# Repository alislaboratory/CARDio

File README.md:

# CARDio: a heart-rate monitor business card

**CARDio** is a PCB business card with a built-in heart-rate monitor. Put your thumb on the sensor and a nervous system drawn in silkscreen lights up in time with your heartbeat, coloured by your heart rate. Lift your thumb and it counts your BPM out on the LEDs.

- **ESP32-C3** (RISC-V, Wi-Fi + BLE) with native USB: one USB-C cable powers and programs it.
- **MAX30102** optical pulse sensor under the "Place Thumb" pad.
- **13 addressable RGB LEDs**: 11 along the brain, spinal cord and nerve roots, and 2 on the back as bullet points for the name and URL.
- Credit-card sized, 4-layer, black and white. Designed in EasyEDA, now also a **KiCad 10** project.

## Using it

1. **Plug it in** with a USB-C cable (any phone charger or computer). A spark climbs the spinal cord, the brain lights up, and the card gives its first heartbeat.
2. **Idle:** the tree glows softly like starlight.
3. **Rest your thumb** lightly on the "Place Thumb" pad and keep still. A violet scan sweeps upward while it finds your pulse. After 5 to 10 seconds, each real heartbeat sends a wave up the tree. The colour tells you the rate:
   - **Blue:** under 60
   - **Teal/green:** resting
   - **Amber:** around 100
   - **Red:** 130+
4. **Lift your thumb** to see your number, counted out from the bottom up one digit at a time. For 72 bpm, 7 lights come on, then a pause, then 2 white lights. A zero shows as one soft flash of the whole tree.

If it doesn't find your pulse, press more lightly and hold still. Warm hands work better than cold ones.

## Repository layout

| | |
| --- | --- |
| [`firmware/`](firmware/) | The firmware (PlatformIO, Arduino on ESP32-C3): heart-rate detection, LED animations, and the boot-pin workaround. [Details →](firmware/README.md) |
| [`hardware/`](hardware/) | KiCad project, original EasyEDA sources, Gerbers/BOM/CPL for ordering, pin map, LED map and errata. [Details →](hardware/README.md) |
| [`docs/images/`](docs/images/) | Photos and renders |
| [`legacy/`](legacy/) | Early Arduino sketches from bring-up, kept for reference |

## Flashing the firmware

Install [PlatformIO](https://platformio.org/) (the VS Code extension or the CLI), plug the card in, then:

```bash
cd firmware
pio run -t upload
```

That's it: no buttons, no adapters. The ESP32-C3 programs over its own USB port. `pio device monitor` opens a serial console. Type `help` for commands, such as `status`, a live `plot` of the sensor signal, or `demo 72` to show off the LEDs without a thumb.

## Why?

I had tinkered with the idea of PCB business cards in the past. My first iteration was essentially just a blank PCB with a silkscreen. It did have circuitry for an ATtiny85 and some NeoPixels, though I never got it to work properly. I liked the idea of handing a business card to somebody that wouldn't be thrown away: one that would actually have a use, like an NFC tag, flashing lights, or an ECG. Perhaps this was a little overkill, but I wanted something to hand to medical professionals or surgeons at conferences that would leave a memorable impression. It also demonstrates my interest in combining medicine and technology, in this case embedded electronics.

## How it works

This was my first PCB that actually does something, so it's not very complicated. USB-C powers the board through two LDOs: one for 3.3 V (the ESP32-C3 and the LEDs) and one for 1.8 V (the MAX30102 sensor). Most of the passive components are the boilerplate to get the microcontroller running. The MAX30102 talks to the ESP32-C3 over I²C, and the RGB LEDs share a single data wire, daisy-chained together. The ESP32-C3 has a built-in USB programmer, so it doesn't need any extra circuitry for that.

The firmware shines infrared light into your thumb and watches how much comes back. Each heartbeat pushes a little more blood into the thumb, which absorbs a little more light, so the signal dips once per beat. It filters that signal, picks out each beat, rejects anything that doesn't fit a steady rhythm, and only shows a heart rate once it has five consistent beats in a row. The [firmware README](firmware/README.md#how-the-heart-rate-is-measured) has the details.

### The one thing that went wrong

Everything worked on the first batch, except for one mistake: the sensor's I²C lines are wired to the ESP32-C3's **boot-mode strapping pins** (GPIO8/9). If the chip resets in the middle of talking to the sensor, it can boot into its bootloader instead of the program, and the card looks dead until you unplug it. The current firmware works around this completely, and the [hardware notes](hardware/README.md#errata-and-ideas-for-rev-31) list it with the other fixes for the next revision.

### Why "Rev 3.0"?

My previous designs were:

- **Rev 1.0:** a simple blank board with a layout for an ATtiny to control LEDs (non-functional)
- **Rev 2.0:** a PCB business card that runs Linux using Onion Omega2 SBCs (not completed)
- **Rev 3.0 (this one):** a PCB business card that measures your heart rate (complete)

## Ideas for Rev 3.1

- Battery (coin cell) and maybe charging
- A small 0.91" OLED for the ECG trace and numbers
- More sensors
- The hardware fixes in the [errata](hardware/README.md#errata-and-ideas-for-rev-31): I²C off the strap pins, a ground plane, and an EN reset capacitor

## License

[MIT](LICENSE), covering the firmware, tools and hardware design files. Build your own, remix it, put your own name on the back.

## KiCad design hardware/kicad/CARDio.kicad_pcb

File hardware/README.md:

# CARDio hardware (Rev 3.0)

A credit-card-sized PCB: an ESP32-C3 reads a MAX30102 pulse sensor under your thumb and drives 13 RGB LEDs, 11 of them laid out along a brain, spinal cord and nerve roots drawn in silkscreen. Power and programming are both over USB-C.

| | |
| --- | --- |
| Size | 85.85 × 54.23 mm (credit card), 1.6 mm, 4 copper layers |
| Finish | Black solder mask, white silkscreen, HASL |
| MCU | ESP32-C3FH4: RISC-V, Wi-Fi + BLE, 4 MB embedded flash, 40 MHz crystal |
| Sensor | MAX30102 pulse oximetry / heart-rate sensor (I²C) |
| LEDs | 13 × WS2812B-2020 addressable RGB (11 front, 2 back) + green power LED |
| USB | USB-C, power + the C3's native USB-Serial/JTAG (no USB-UART chip), USBLC6-2SC6 ESD protection |
| Power | 5 V USB → AMS1117-3.3 (MCU, LEDs, sensor LEDs) and AMS1117-1.8 (sensor core) |
| Antenna | On-board inverted-F PCB antenna (ANT1) |

## Files

| Folder | What's in it |
| --- | --- |
| [`kicad/`](kicad/) | **The KiCad 10 project**: schematic, PCB, design rules, and project-local symbol and footprint libraries (`CARDio.kicad_sym`, `CARDio.pretty`), so it opens anywhere without extra libraries. Start here to modify the board. |
| [`CARDio_schematic.pdf`](CARDio_schematic.pdf) | The schematic as a PDF |
| [`fabrication/`](fabrication/) | What the cards were made from: Gerbers + drill (`CARDio_Rev3.0_gerbers.zip`), BOM and pick-and-place (CPL) for JLCPCB assembly. |
| [`easyeda/`](easyeda/) | The original EasyEDA Standard sources the board was designed in (open them via *File → Open → EasyEDA…* in EasyEDA). |
| [`tools/`](tools/) | The scripts used to convert the design to KiCad and to verify the conversion. |

## Block diagram

```mermaid
flowchart LR
    USB["USB-C<br/>(5 V, D+/D−)"] --> ESD["USBLC6-2SC6<br/>ESD"]
    ESD -- "D+/D− (GPIO19/18)" --> MCU
    USB -- 5 V --> LDO33["AMS1117-3.3"] -- "3.3 V" --> MCU["ESP32-C3FH4"]
    USB -- 5 V --> LDO18["AMS1117-1.8"] -- "1.8 V" --> SENS["MAX30102<br/>pulse sensor"]
    LDO33 -- "3.3 V (LED drive)" --> SENS
    LDO33 -- "3.3 V" --> LEDS["13 × WS2812B-2020"]
    MCU -- "I²C: SDA GPIO9, SCL GPIO8" --> SENS
    MCU -- "data GPIO3" --> LEDS
    MCU --- ANT["PCB inverted-F antenna"]
```

## ESP32-C3 pin map

| GPIO | Net | Used for |
| --- | --- | --- |
| 3 | `GPIO3` | WS2812B chain data in (to LED9) |
| 8 | `SCL` | MAX30102 I²C clock, 4.7 kΩ pull-up (R3). **Boot strapping pin**, see errata. |
| 9 | `SDA` | MAX30102 I²C data, 4.7 kΩ pull-up (R4). **BOOT strapping pin**, see errata. |
| 18 / 19 | `USB-D−` / `USB-D+` | Native USB (programming + serial console) |
| 20 / 21 | `U0RXD` / `U0TXD` | UART0, labelled but not broken out (TX through R1, 499 Ω) |
| 0, 1, 2, 4–7, 10 | `GPIOx` | Unused (net labels only) |
| EN | | 5.1 kΩ pull-up (R7) |

The MAX30102's `INT#` pin has a pull-up (R2) but isn't connected to the ESP32, so firmware has to poll the sensor.

## LED chain

The data line goes `GPIO3 → LED9 → LED10 → LED3 → LED1 → LED2 → LED4 → LED6 → LED5 → LED7 → LED8 → LED12 → LED13 → LED14`. LED11 is the PWR indicator, not part of the chain.

| Chain index | Ref | Where |
| --- | --- | --- |
| 0 | LED9 | Brain, top centre |
| 1 | LED10 | Brain, centre |
| 2 | LED3 | Brainstem junction |
| 3 | LED1 | Spinal cord |
| 4 | LED2 | Spinal cord, lower |
| 5 | LED4 | Base of the cord |
| 6 | LED6 | Spinal cord, upper |
| 7 | LED5 | Right lobe, inner |
| 8 | LED7 | Right lobe, outer |
| 9 | LED8 | Left lobe |
| 10 | LED12 | Nerve root branch |
| 11 | LED13 | **Back**, bullet beside the name |
| 12 | LED14 | **Back**, bullet beside the URL |

The firmware's [`leds.cpp`](../firmware/src/leds.cpp) holds the same map with each LED's position, which it uses to send waves along the tree.

## Ordering boards

The Rev 3.0 cards were made and assembled by JLCPCB from the files in [`fabrication/`](fabrication/):

1. Upload `CARDio_Rev3.0_gerbers.zip`. Choose **4 layers, 1.6 mm, black solder mask, white silkscreen**.
2. For assembly (both sides: the two back LEDs are on the bottom), upload `CARDio_Rev3.0_BOM.csv` and `CARDio_Rev3.0_CPL.csv`. The BOM has LCSC part numbers for every part.

To generate fresh outputs from KiCad instead (after changes), use *File → Fabrication Outputs* in the PCB editor, or:

```bash
kicad-cli pcb export gerbers -o gerbers/ kicad/CARDio.kicad_pcb
kicad-cli pcb export drill -o gerbers/ kicad/CARDio.kicad_pcb
kicad-cli pcb export pos --format csv --units mm -o CARDio_CPL.csv kicad/CARDio.kicad_pcb
```

## Errata and ideas for Rev 3.1

1. **The sensor's I²C lines are on boot strapping pins (GPIO8/GPIO9).** At reset, the ESP32-C3 reads GPIO9 to choose between running the program and the ROM bootloader. If the chip resets in the middle of an I²C read, the MAX30102 can be left holding SDA low and the card boots into the bootloader instead of the firmware, so it looks dead until it's unplugged. The [firmware](../firmware/README.md#the-soft-brick-explained) works around this. **Fix:** move SDA/SCL to free pins (e.g. GPIO4/GPIO5).
2. **GPIO2 (another strapping pin) floats.** Espressif recommends pulling it high. **Fix:** add a 10 kΩ pull-up.
3. **EN has no reset delay capacitor.** Espressif's reference circuit puts an RC (e.g. 10 kΩ + 1 µF) on EN so the chip starts only once the supply is stable. **Fix:** add a 1 µF cap from EN to GND.
4. **No ground plane.** All four layers carry tracks only; there are no copper pours. A solid GND pour (at least on one inner layer) would help the antenna, the sensor's analog front end and EMI. Keep the pour clear of the area under and around the antenna.
5. **WS2812B-2020s run from 3.3 V**, below the 3.7 V minimum in their datasheet. They work, but blues can look weak, and colour accuracy may vary between parts. **Fix:** power them from 5 V (with a level shifter on the data line), or choose 3.3 V-rated LEDs.
6. **MAX30102 `INT#` isn't connected.** Routing it to a GPIO would let firmware sleep until a sample is ready, instead of polling.
7. **The silkscreen says "REV 1.0"**, but this is the third CARDio design, Rev 3.0 (see [the main README](../README.md#why-rev-30)).

## About the KiCad conversion

The board was designed in EasyEDA Standard and converted to KiCad 10 for this repo. KiCad's importers get the routing and the parts right, but on this design they silently lose things. Three scripts in [`tools/`](tools/) repair them and can be re-run from a fresh import.

**PCB.** [`fix_easyeda_import.py`](tools/fix_easyeda_import.py) runs after `kicad-cli pcb import`. EasyEDA draws some copper and paste as filled regions inside footprints; KiCad turns those into footprint zones, which it never plots. The script:

- Restores the **antenna copper**. Without it, a board made from the KiCad files would have no antenna. It's modelled as a net-tie footprint, since an inverted-F antenna is shorted to ground by design.
- Restores the **solder-paste apertures** of every LCSC part with custom (notched) paste shapes: all the passives, the ESP32-C3 and the USB-C socket.
- Hides reference/value labels EasyEDA kept hidden.
- Refits text set in *Source Code Pro* (name, URL, "Place Thumb" and so on) to the exact size and position EasyEDA used. The font is embedded in the board file.
- Records the real stackup (4 layers, black mask, white silk) and the design rules the board was made to (0.16 mm tracks, 0.15 mm clearance), with Power/Ground net classes matching the original.
- Saves the footprints into the project library `CARDio.pretty`, keeping genuinely different variants separate (e.g. the flipped back-side LEDs), and re-links every footprint to it.
- Makes **one deliberate change**: the "3V3" copper label moved 0.14 mm, because it sat 0.026 mm from a GND track.

**Schematic.** KiCad imports EasyEDA schematics only through the GUI (*Schematic Editor → File → Import → Non-KiCad Schematic*). [`fix_easyeda_schematic.py`](tools/fix_easyeda_schematic.py) runs on the result:

- **Adds 32 missing junctions.** EasyEDA connects a wire that ends on the middle of another wire; KiCad needs a junction dot there. Without them, 13 nets (GND, VCC, 1V8, +5V, SDA, the crystal and antenna networks, and others) came out split.
- **Sets real electrical pin types.** EasyEDA doesn't store them, so every passive pin came in as "input" and every IC pin as "unspecified". Now regulator outputs and USB VBUS/GND are power outputs, IC supply pins are power inputs, and so on, so ERC means something. It also adds a PWR_FLAG on the ESP32's LC-filtered RF supply.
- Adds no-connect flags on pins unused by design: sensor N.C. pins, the ESP32's internal-flash SPI pins, USB SBU/shell, the last LED's data-out.
- Renames the power LED to `PWR`, matching the PCB and the ordered BOM, and keeps EasyEDA's page frame out of the BOM.
- Folds the importer's per-instance symbol copies into the project library `CARDio.kicad_sym` and fills in every symbol's footprint.

[`sync_pcb_from_schematic.py`](tools/sync_pcb_from_schematic.py) then does the scriptable half of *Update PCB from Schematic*: it renames the board's nets to the schematic's and copies part fields onto the footprints. It first checks that every net groups exactly the same pads in both.

### Verification

Gerbers plotted from the KiCad board were compared with the Gerbers JLCPCB actually made the cards from, using [`compare_gerbers.py`](tools/compare_gerbers.py):

| Layer | Differing area |
| --- | --- |
| Board outline | 0.00 % |
| Top / inner 1 / inner 2 / bottom copper | 0.03 % (the moved label) / 0.00 % / 0.00 % / 0.00 % |
| Top / bottom solder paste | 0.00 % / 0.00 % |
| Top / bottom solder mask | 0.16 % / 2.25 % (KiCad also opens mask over the USB-C socket's two plastic locating-peg holes) |
| Top / bottom silkscreen | 0.01 % / 2.4 % (sub-pixel font rasterisation) |

| Check | Result |
| --- | --- |
| DRC | **0 errors, 0 unconnected.** 3 warnings for the three smallest silkscreen labels ("ESP32-C3", "REV 1.0", "Place Thumb"), which printed legibly on the real cards. |
| ERC | **0 errors.** 10 warnings: the labels on the unused GPIOs, kept from the original design as documentation. |
| Schematic ↔ PCB parity | **0 issues.** All 35 multi-pin nets connect the same pads in both. |

Silkscreen-over-copper checks are turned off for this project: the brain/nerve artwork deliberately runs under the LED footprints, and the fab clips silkscreen at pad openings.

Cosmetic leftovers from the import, all harmless and easy to tidy by hand in KiCad: a few power symbols show their labels upside down, and EasyEDA's page frame is drawn inside KiCad's.

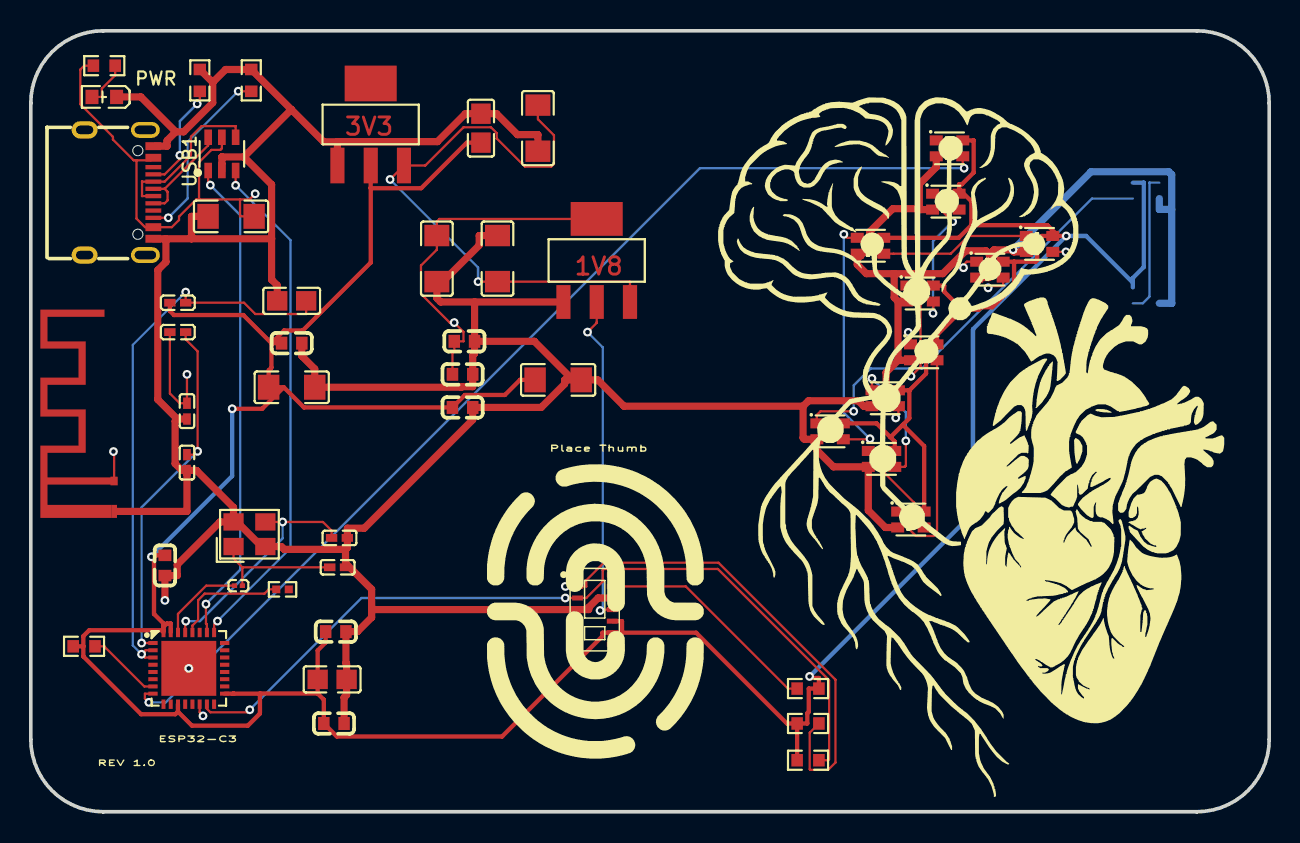
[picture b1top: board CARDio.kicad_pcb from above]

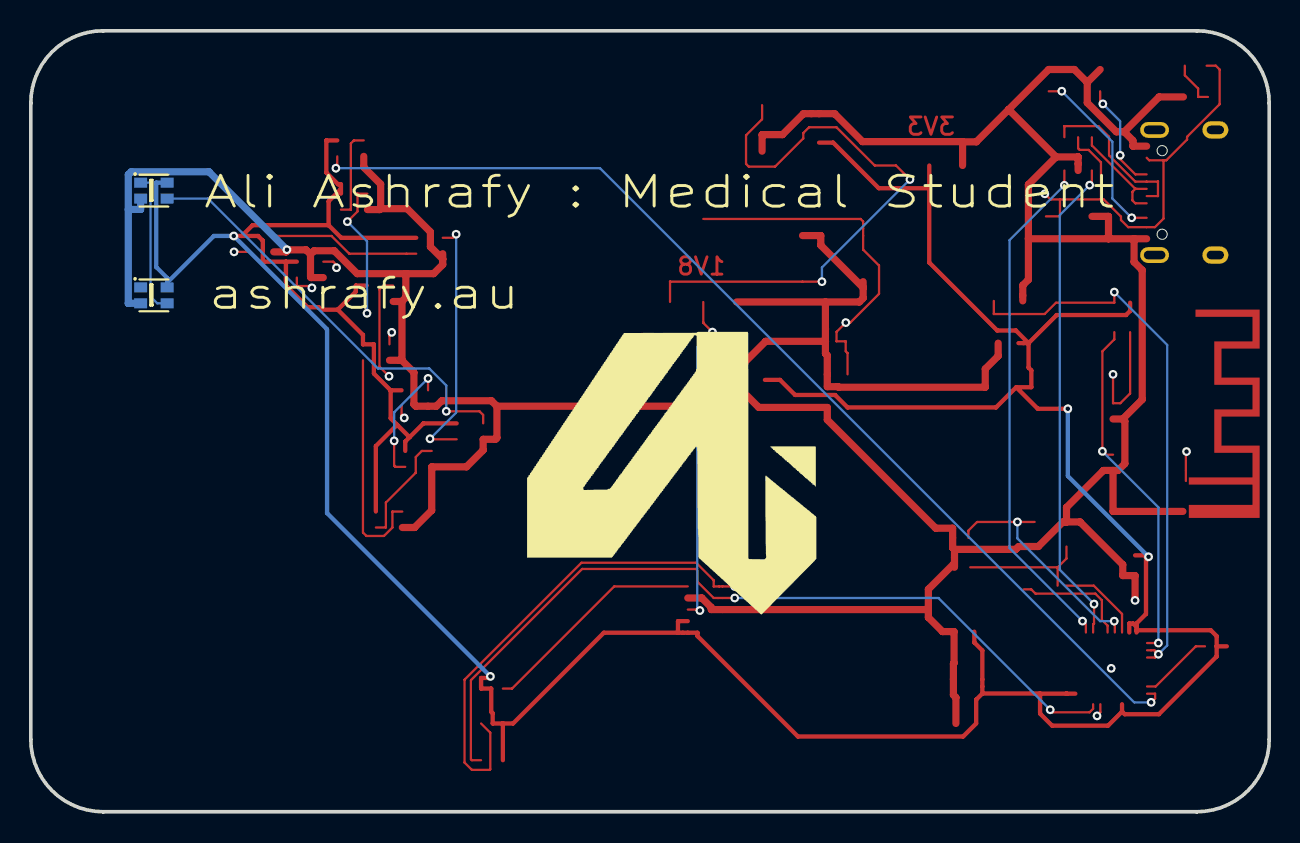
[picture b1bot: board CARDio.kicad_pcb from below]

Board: 4 copper layers, 85.6 x 54.0 mm, 53 parts (2 on the bottom side), 35 nets.

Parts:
ANT1: WIFI_ANTENNA; WIFI_ANTENNA_MIFA_INVERTED_F_ANTENNA
C1: 10nF; C0603
C2, C7: 1uF; C0805
C3, C4: 10pF; C0402
C5, C6, C8, C13, C14: 100nF; C0603
C9, C15, C16, C18, C19, C20: 10uF; C1206
C10, C11: 3.3pF; C0402
C12: 4.7uF; C0603
C17: 22uF; C0805
D1: USBLC6-2SC6; SOT-23-6_L2.9-W1.6-P0.95-LS2.8-BL
L1: 24nH; L0201
L3, L4: 2.2nH; L0402
LED1, LED2, LED3, LED4, LED5, LED6, LED7, LED8, LED9, LED10, LED12: WS2812B-2020; LED-SMD_4P-L2.0-W2.0-TL_WS2812B-2020
LED13, LED14: WS2812B-2020; LED-SMD_4P-L2.0-W2.0-TL_WS2812B-2020_v2
PWR: A-SP192DGHC-C01-4T; LED0603-FD
R1: 499Ω; R0402
R2, R3, R4: 4.7kΩ; R0603
R5, R6, R7: 5.1kΩ; R0603
R8: 470Ω; R0603
U1: ESP32-C3FH4; QFN-32_L5.0-W5.0-P0.50-TL-EP3.7
U2: MAX30102EFD+T_C6454833; OESIP-14_L5.6-W3.3-P0.80-TL
U3: 40MHz; CRYSTAL-SMD_4P-L3.2-W2.5-BL
U4: AMS1117-3.3_C347222; SOT-223-4_L6.5-W3.5-P2.30-LS7.0-BR
U5: AMS1117-1.8_C5250991; SOT-223-3_L6.7-W3.7-P2.30-LS7.0-BR
USB1: TYPE-C 16PIN 2MD(073); USB-C-SMD_TYPE-C-6PIN-2MD-073

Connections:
1V8: C12.1, C13.1, C19.1, U2.11, U5.2, U5.4
+5V: C16.1, C18.2, C20.2, D1.5, R8.1, U4.3, U5.3, USB1.2, USB1.11
GND: ANT1.GND, C1.2, C2.2, C3.2, C4.2, C5.1, C6.2, C7.1, C8.2, C9.2, C10.1, C11.1, C12.2, C13.2, C14.2, C15.2, C16.2, C17.1, C18.1, C19.2, C20.1, D1.2, LED1.2, LED2.2, LED3.2, LED4.2, LED5.2, LED6.2, LED7.2, LED8.2, LED9.2, LED10.2, LED12.2, LED13.2, LED14.2, PWR.2, R5.1, R6.1, U1.33, U2.4, U2.12, U3.2, U3.4, U4.1, U5.1, USB1.1, USB1.12
GPIO3: LED9.3, U1.8
unnamed: ANT1.ANT, C10.2, L4.1
unnamed: C3.1, L1.2, U3.1
unnamed: C7.2, L3.2, U1.2, U1.3
unnamed: LED1.3, LED3.1
unnamed: LED1.1, LED2.3
unnamed: LED2.1, LED4.3
unnamed: LED4.1, LED6.3
unnamed: LED5.3, LED6.1
unnamed: LED5.1, LED7.3
unnamed: LED7.1, LED8.3
unnamed: LED9.1, LED10.3
unnamed: LED3.3, LED10.1
unnamed: LED8.1, LED12.3
unnamed: LED12.1, LED13.3
unnamed: LED13.1, LED14.3
unnamed: PWR.1, R8.2
unnamed: R7.2, U1.7
unnamed: C11.2, L4.2, U1.1
unnamed: R1.1, U1.28
unnamed: C4.1, U1.29, U3.3
unnamed: L1.1, U1.30
unnamed: R2.1, U2.13
unnamed: R5.2, USB1.4
unnamed: R6.2, USB1.10
unnamed: D1.4, USB1.5, USB1.7
unnamed: D1.6, USB1.6, USB1.8
SCL: R3.2, U1.14, U2.2
SDA: R4.2, U1.15, U2.3
USB-D+: D1.1, U1.26
USB-D-: D1.3, U1.25
VCC: C1.1, C2.1, C5.2, C6.1, C8.1, C9.1, C14.1, C15.1, C17.2, L3.1, LED1.4, LED2.4, LED3.4, LED4.4, LED5.4, LED6.4, LED7.4, LED8.4, LED9.4, LED10.4, LED12.4, LED13.4, LED14.4, R2.2, R3.1, R4.1, R7.1, U1.11, U1.17, U1.31, U1.32, U2.9, U2.10, U4.2

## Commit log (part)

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2025-08-15 rev 3.0 init commit + readme
2025-08-15 readme changes
2025-08-15 added gif to readme
2025-08-15 update file structure
2025-08-15 gitignore
2025-09-01 images
